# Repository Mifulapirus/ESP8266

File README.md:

# README #
ESP8266 Arduino library

### What is this repository for? ###
* This ibrary allows you to easily work with the ESP8266 from any Arduino.

### Set Up ###
* Copy the whole ESP8266/Arduino Library folder into your Documents/Arduino forlder.
* Make sure you add SoftwareSerial.h to your sketch as well as this ESP8266.h.

### Contact ###
* @mifulapirus

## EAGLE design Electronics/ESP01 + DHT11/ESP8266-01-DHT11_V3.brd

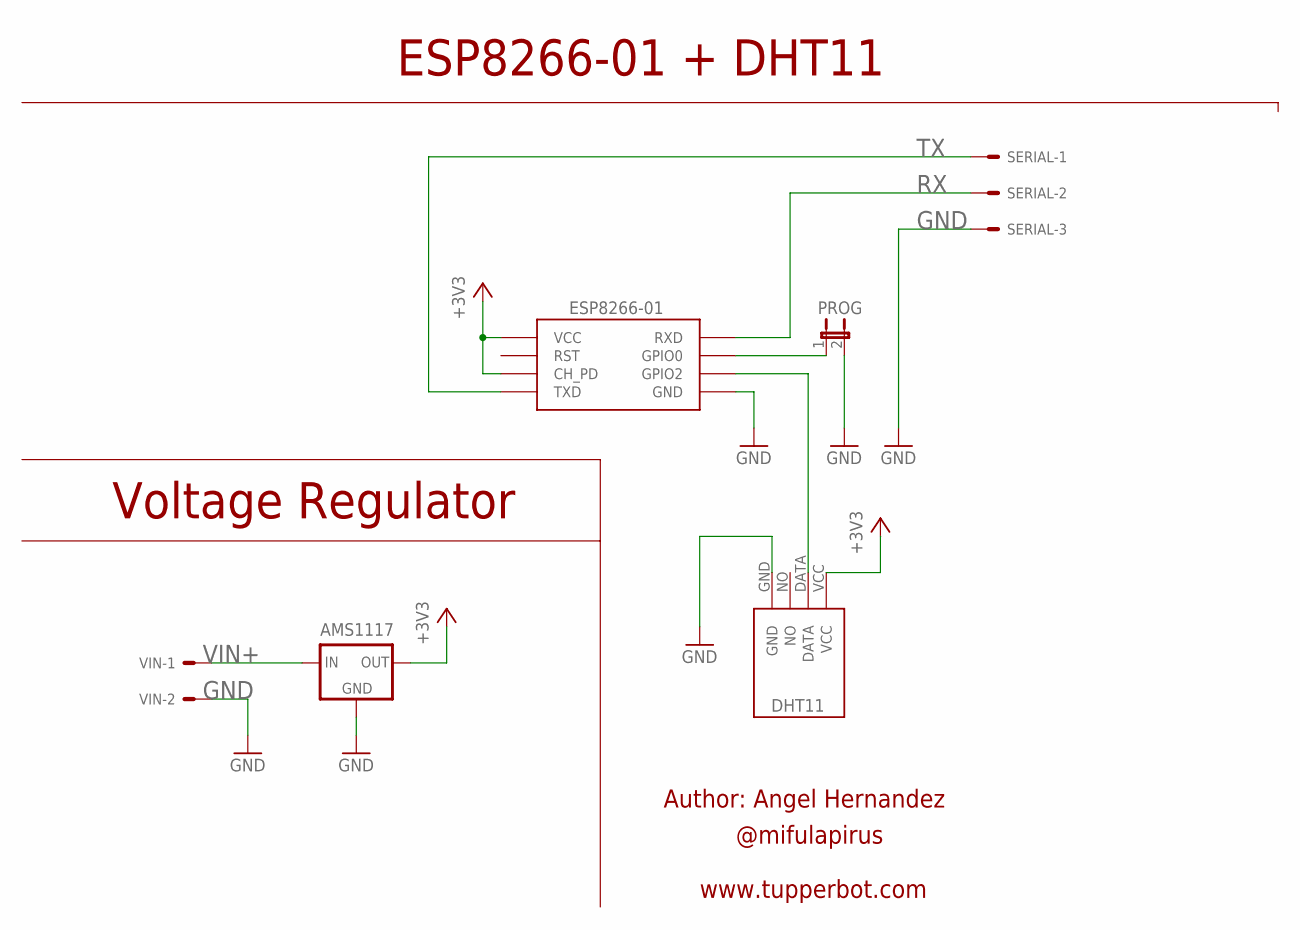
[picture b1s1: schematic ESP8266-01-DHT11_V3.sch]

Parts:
AMS1117: LM1117; SOT223
ESP8266-01: ESP-01
PROG: JP1E; JP1
SERIAL: 22-27-2031-03; 6410-03
U$2: DHT11-PION.
VIN: 22-27-2021-02; 6410-02

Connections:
+3V3: AMS1117.2 (OUT), ESP8266-01.CH_PD, ESP8266-01.VCC, U$2.VCC
GND: AMS1117.1 (GND), ESP8266-01.GND, PROG.2, SERIAL.3, U$2.GND, VIN.2
unnamed: ESP8266-01.GPIO0, PROG.1
unnamed: ESP8266-01.GPIO2, U$2.DATA
RX: ESP8266-01.RX (RXD), SERIAL.2
TX: ESP8266-01.TX (TXD), SERIAL.1
VIN+: AMS1117.3 (IN), VIN.1

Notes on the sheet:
Voltage Regulator
ESP8266-01 + DHT11
Author: Angel Hernandez
@mifulapirus
www.tupperbot.com

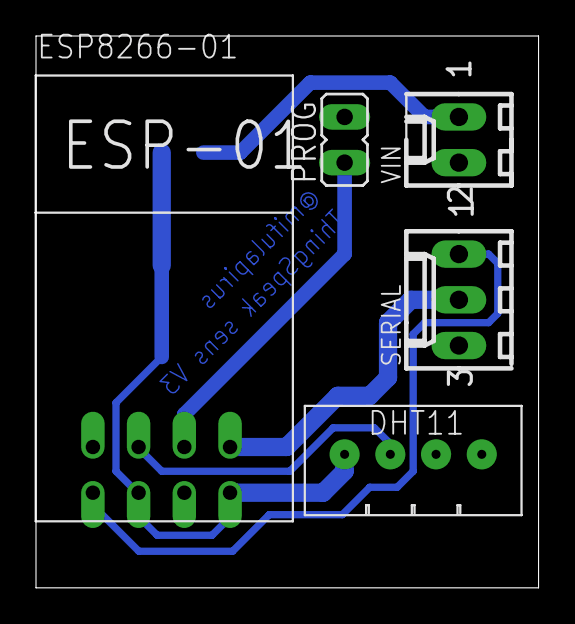
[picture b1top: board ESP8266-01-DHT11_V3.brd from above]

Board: 2 copper layers, 27.9 x 30.7 mm, 6 parts (1 on the bottom side), 7 nets.

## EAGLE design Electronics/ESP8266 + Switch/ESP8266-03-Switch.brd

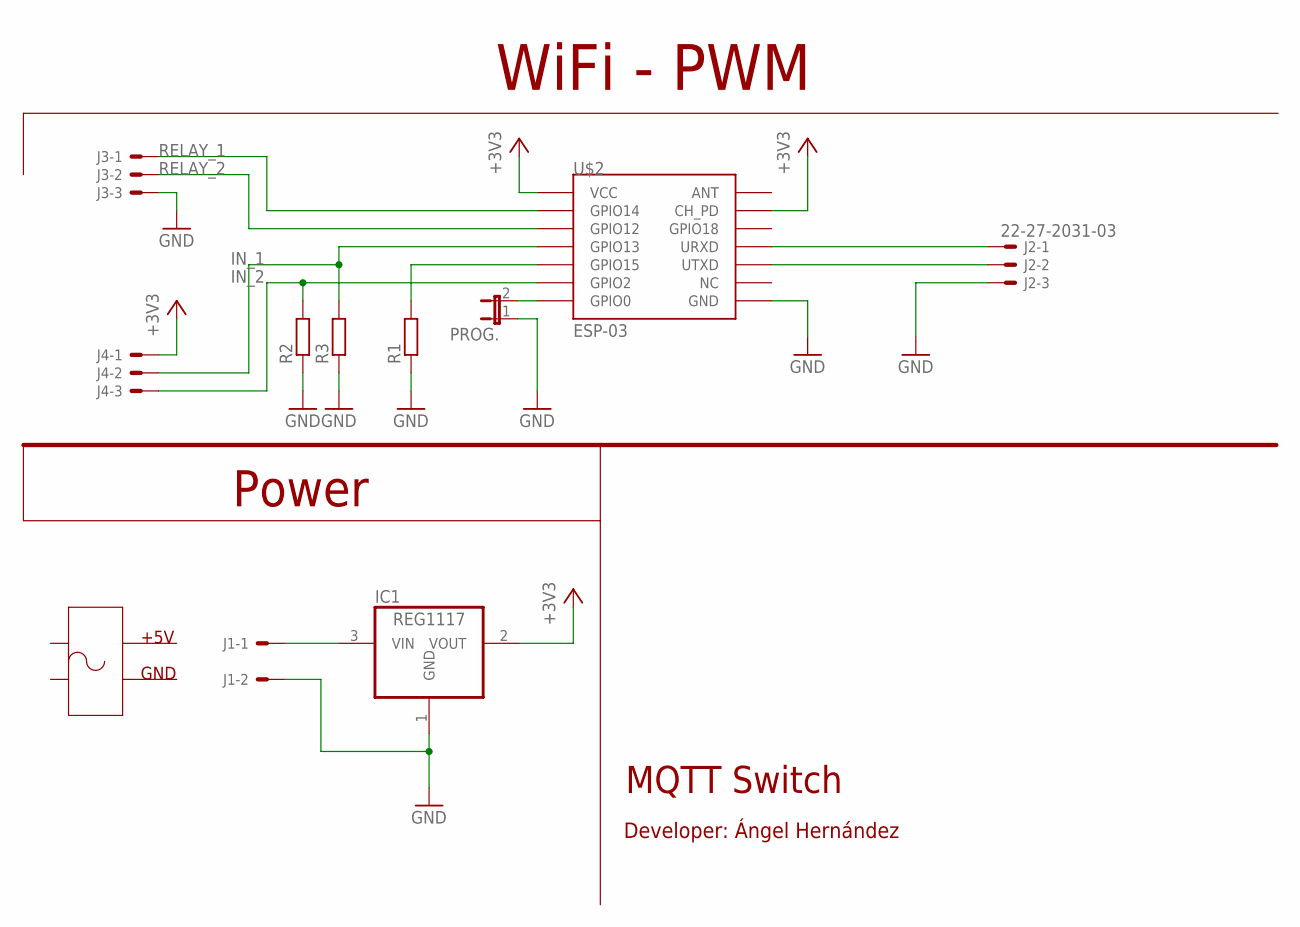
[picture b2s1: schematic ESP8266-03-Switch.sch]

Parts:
IC1: REG1117; SOT223
J1: 22-27-2021-02; 6410-02
J2, J3, J4: 22-27-2031-03; 6410-03
PROG.: JP1E; JP1
R1, R2, R3: R-EU_0204/7; 0204/7
U$2: ESP-03

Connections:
+3V3: IC1.2 (VOUT), J4.1, U$2.CH_PD, U$2.VCC
GND: IC1.1 (GND), J1.2, J2.3, J3.3, PROG..1, R1.1, R2.1, R3.1, U$2.GND
IN_1: J4.2, R3.2, U$2.GPIO13
IN_2: J4.3, R2.2, U$2.GPIO2
unnamed: IC1.3 (VIN), J1.1
unnamed: PROG..2, U$2.GPIO0
unnamed: J2.1, U$2.URXD
unnamed: J2.2, U$2.UTXD
unnamed: R1.2, U$2.GPIO15
RELAY_1: J3.1, U$2.GPIO14
RELAY_2: J3.2, U$2.GPIO12

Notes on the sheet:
WiFi - PWM
Power
MQTT Switch
Developer: Ángel Hernández
+5V
GND

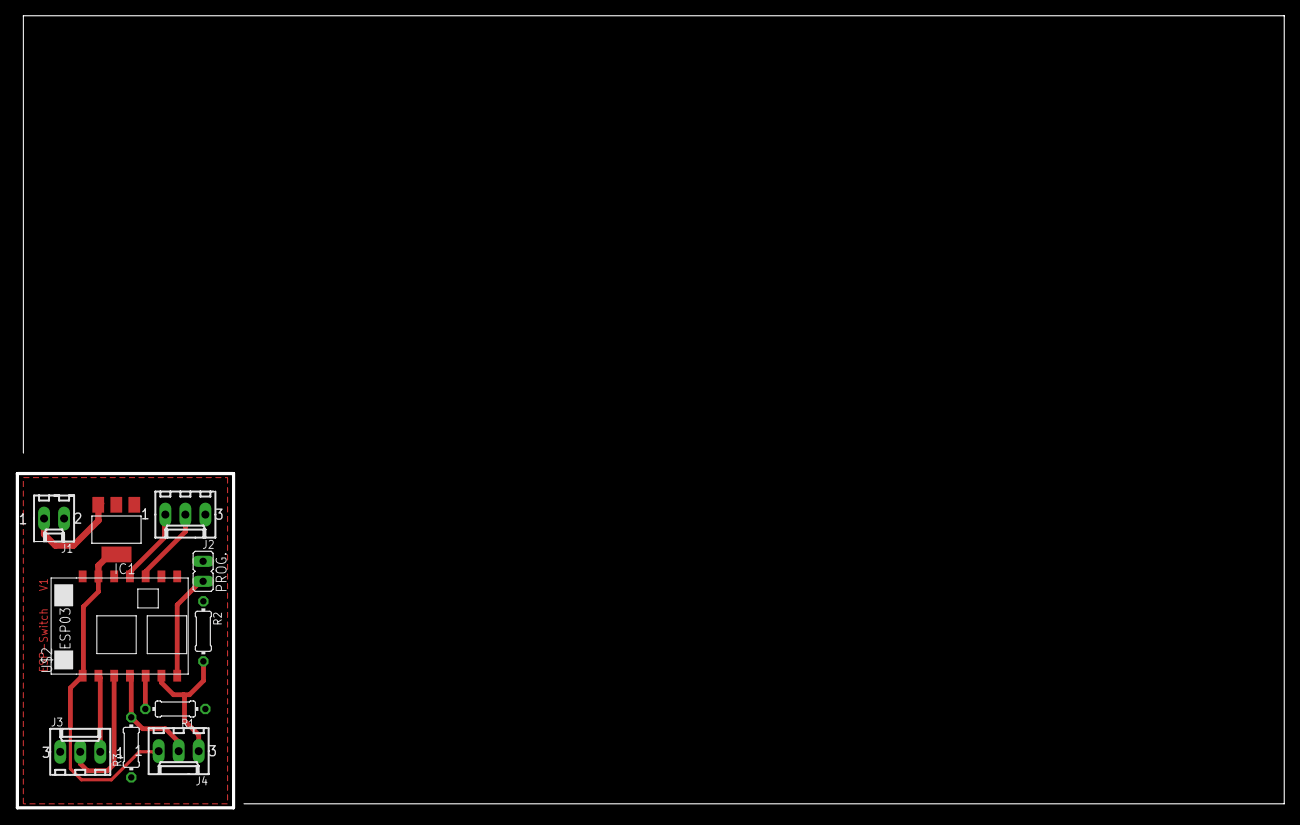
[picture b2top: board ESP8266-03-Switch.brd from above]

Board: 2 copper layers, 160.8 x 100.5 mm, 10 parts (0 on the bottom side), 11 nets.

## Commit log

2015-02-07 Initial commit - Needs a lot of improvement - Requires to import SoftwareSerial or add SoftwareSerial.h and SoftwareSerial.cpp to the same project folder
2015-02-08 Regular Commit - Better response management - Added definitions for AT responses and commands - Many other improvements
2015-02-09 Regular Commit - Added Init procedure - Added Baud to constructor - Cleaned examples
2015-02-09 Regular Commit - Added good header - Cleaned up the code
2015-02-10 Regular Commit - Added listen() to constructor - Fixed a bug that prevented the reset line to work (line 23) - changed init, reboot, reset and connect function names
2015-02-11 Docummentation - Added a lot of documentation and some TODOs - Fixed some bugs on the Echo example.
2015-02-12 Bug Fixing - Reserved some memory for the wifiLongMessage - Return errors
2015-02-12 Regular Commit - Now with the proper file
2015-02-20 Regular Commit - set return values as byte - create the closeServer function
2015-02-20 Regular Commit - Deletedsome useless files.
2015-05-25 -Added electronics for DHT11 & ESP01
2015-05-26 Added RGB-Lamp project
2015-05-27 Added ESP + Switch
2015-06-17 - new Switch and RGB boards
2015-09-15 - Updated electronics
